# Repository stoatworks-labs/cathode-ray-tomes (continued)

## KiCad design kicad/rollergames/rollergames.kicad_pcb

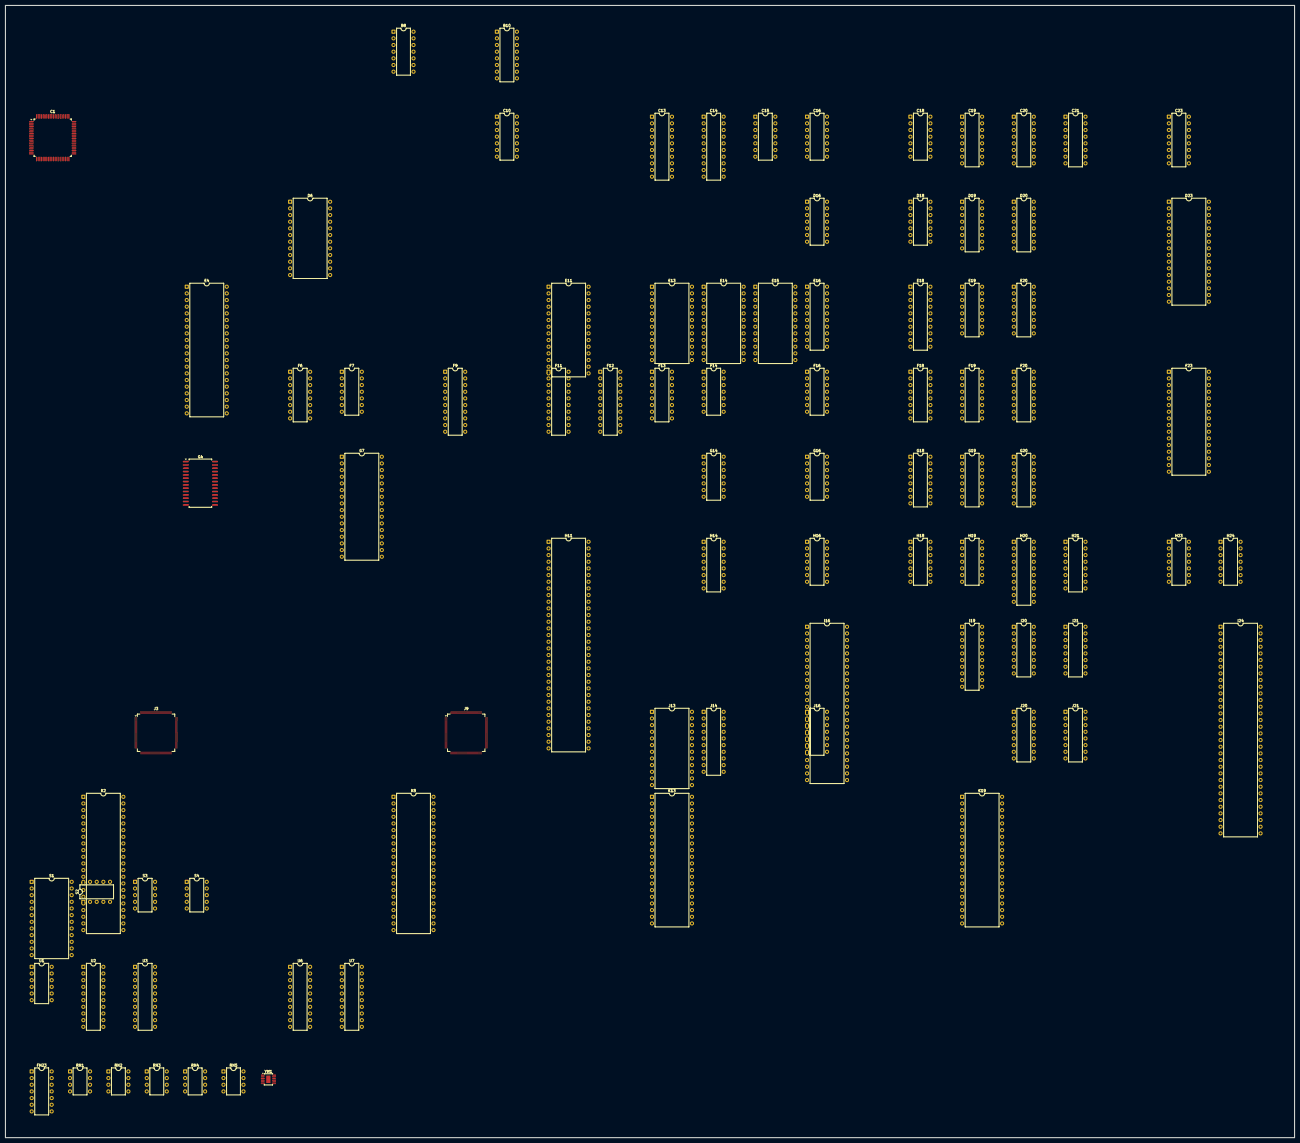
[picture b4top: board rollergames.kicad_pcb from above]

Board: 2 copper layers, 491.3 x 431.5 mm, 88 parts (0 on the bottom side), 516 nets, no tracks yet.

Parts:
B8: LM324; DIP-14_W7.62mm
B10: YM3012; DIP-16_W7.62mm
C1: 053260; PQFP-80_14x14mm_P0.65mm
C10: LM324; DIP-14_W7.62mm
C13, C14: 74LS273; DIP-20_W7.62mm
C15, C16, C18: 74LS07; DIP-14_W7.62mm
C19, C20, C21, C23: 74LS253; DIP-16_W7.62mm
D6: YM3812-3526; DIP-24_W15.24mm
D16: 74LS07; DIP-14_W7.62mm
D18: 74LS32; DIP-14_W7.62mm
D19, D20: 74LS257; DIP-16_W7.62mm
D23: 23C4000; DIP-32_W15.24mm
E4: Z80CPU; DIP-40_W15.24mm
E11: 27256; DIP-28_W15.24mm
E13: MB9416; DIP-24_W15.24mm
E14, E15: SRAM2K8B; DIP-24_W15.24mm
E16, E18: 74LS245; DIP-20_W7.62mm
E19: 74LS157; DIP-16_W7.62mm
E20: 63S141; DIP-16_W7.62mm
F6, F13: 74LS138; DIP-16_W7.62mm
F7, F14: 74LS04; DIP-14_W7.62mm
F9: 74LS245; DIP-20_W7.62mm
F11, F12: PAL16L8; DIP-20_W7.62mm
F16: 74LS08; DIP-14_W7.62mm
F18, F19: 74LS157; DIP-16_W7.62mm
F20: 74LS399; DIP-16_W7.62mm
F23: 23C4000; DIP-32_W15.24mm
FH23: 74LS08; DIP-14_W7.62mm
G4: MB8464A; SOP-28_8.4x18.16mm_P1.27mm
G7: 27C1000; DIP-32_W15.24mm
G14: 74LS74; DIP-14_W7.62mm
G16: 74LS32; DIP-14_W7.62mm
G18: 74LS174; DIP-16_W7.62mm
G19: 74LS367; DIP-16_W7.62mm
G20: 74LS399; DIP-16_W7.62mm
H11: 053248; DIP-64_W15.24mm
H14: 74LS367; DIP-16_W7.62mm
H16: 74LS04; DIP-14_W7.62mm
H18, H19: 74LS74; DIP-14_W7.62mm
H20: 74LS273; DIP-20_W7.62mm
H21: 74LS399; DIP-16_W7.62mm
H23: 74LS08; DIP-14_W7.62mm
H24: 74LS164; DIP-14_W7.62mm
I16: DIP-48_W15.24mm
I19: 74LS244; DIP-20_W7.62mm
I20: 74LS175; DIP-16_W7.62mm
I21: 74LS174; DIP-16_W7.62mm
I24: DIP-64_W15.24mm
J3: 053244; TQFP-120_14x14mm_P0.4mm
J9: 053245; TQFP-120_14x14mm_P0.4mm
J13: SRAM2K8B; DIP-24_W15.24mm
J14: 74LS245; DIP-20_W7.62mm
J16: 74LS04; DIP-14_W7.62mm
J20: 74LS175; DIP-16_W7.62mm
J21: 74LS174; DIP-16_W7.62mm
K2, K8: HN624116P; DIP-42_W15.24mm
K13, K19: 23C4100; DIP-40_W15.24mm
RN1, RN2, RN3, RN4, RN5: KONAMI_005273; DIP-8_W7.62mm
S1: 051550; DIP-24_W15.24mm
S2, S3, S4: 052535; DIP-10_W7.62mm
U1: MB3733-31; DIP-12_W7.62mm
U2, U3, U6, U7: 74LS244; DIP-20_W7.62mm
YM1: YM3014; MSOP-12-1EP_3x4.039mm_P0.65mm_EP1.651x2.845mm

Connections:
/+12V: S1.19, U1.11
/CLK1: I16.8, I24.2
/CLK2: C13.11, C14.11, F20.9, G20.9, H16.1, H19.3, H20.11, I16.9, J3.10, J9.10
/CLK4: I16.11, I24.63, J16.1
/COIN_CNT_1: S1.22, S1.23
/COIN_CNT_2: S1.20, S1.21
/CPU~EN: D19.2, G16.2, J9.26
/DB0: C1.8, C21.9, D19.9, J3.29, J14.2
/DB1: C1.9, C21.7, D19.12, J3.28, J14.3
/DB2: C1.10, C23.9, D19.7, J3.27, J14.4
/DB3: C1.11, C23.7, D19.4, J3.26, J14.5
/DB4: C1.13, C20.9, D20.9, J3.25, J14.6
/DB5: C1.14, C20.7, D20.12, J3.24, J14.7
/DB6: C1.15, C19.9, D20.7, J3.23, J14.8
/DB7: C1.16, C19.7, D20.4, J3.22, J14.9
/DTAC: F16.3, H11.49
/G18P7: E20.15, F12.2, G18.7
/G18P15: G16.4, G18.15
/IO_Cabinet/DW1_4: C23.6, C23.10
/IO_Cabinet/SMU: C19.14, C20.14, C21.14, C23.14, D19.1, D20.1, F14.4
/IO_Cabinet/SMUB: C19.2, C20.2, C21.2, C23.2, F14.2
/IO_Cabinet/VCC: C19.16, C20.16, C21.16, C23.16, D19.5, D19.11, D19.14, D19.16, D20.2, D20.5, D20.11, D20.14, D20.16
/M12B: H16.3, H16.12, H19.11, I21.9, J3.12, J9.12, J21.9
/MAIN_A0: D18.5, F7.13, F14.3, G4.2, G4.10, G4.23, G7.4, G7.12, G7.25, H11.14, I16.42, J3.19, J9.9, J21.3
/MAIN_A1: C1.18, F14.1, F18.2, G4.9, G7.11, H11.13, I16.41, J3.18, J9.25, J21.4
/MAIN_A2: F18.5, G4.8, G7.10, H11.12, I16.40, J3.17, J9.24, J21.6
/MAIN_A3: F18.11, G4.7, G7.9, H11.11, I16.38, J3.15, J9.23, J21.11
/MAIN_A4: F13.1, F18.14, G4.6, G7.8, H11.9, J9.22, J21.13
/MAIN_A5: F12.11, F13.2, F19.2, G4.5, G7.7, H11.8, J9.20, J21.14
/MAIN_A6: F12.9, F13.3, F19.5, G4.4, G7.6, H11.7, I21.3, J9.19
/MAIN_A7: F12.8, F19.11, G4.3, G7.5, H11.6, I21.4, J9.18
/MAIN_A8: F12.7, F19.14, G4.25, G7.27, H11.62, I21.6, J9.17
/MAIN_A9: E19.2, F12.6, G4.24, G7.26, H11.61, I21.11, J9.15
/MAIN_A10: E19.5, F12.5, G4.21, G7.23, H11.60, I21.13, J9.14
/MAIN_A11: F12.4, H11.59
/MAIN_A12: F11.5, F12.3, H11.56
/MAIN_A13: F11.4, H11.55
/MAIN_A14: F11.3, H11.54
/MAIN_A15: F11.2, H11.53
/MAIN_A16: F11.9, H11.38
/MAIN_A17: F11.8, H11.39
/MAIN_A18: F11.7, H11.40
/MAIN_A19: F11.6, H11.41
/MAIN_AB0: F11.14, G7.28
/MAIN_AB1: F11.15, G7.29
/MAIN_AB2: F11.16, G7.3
/MAIN_AB3: F11.17, G7.2
/MAIN_D0: F9.18, G4.11, G7.13, H11.21
/MAIN_D1: F9.17, G4.12, G7.14, H11.22
/MAIN_D2: F9.16, G4.13, G7.15, H11.23
/MAIN_D3: F9.15, G4.15, G7.17, H11.24
/MAIN_D4: F9.14, G4.16, G7.18, H11.27
/MAIN_D5: F9.13, G4.17, G7.19, H11.28
/MAIN_D6: F9.12, G4.18, G7.20, H11.29
/MAIN_D7: F9.11, G4.19, G7.21, H11.30
/MOE: C19.1, C19.15, C20.1, C20.15, C21.1, C21.15, C23.1, C23.15, F13.10
/Main/CRES: G18.1, H14.4, I16.12
/Main/DB0: F9.2, G18.3, I16.13
/Main/DB1: F9.3, G18.4, I16.14
/Main/DB2: F9.4, G18.6, I16.15
/Main/DB3: F9.5, G18.11, I16.16
/Main/DB4: F9.6, G18.13, I16.18
/Main/DB5: F9.7, G18.14, I16.19
/Main/DB6: F9.8, I16.20
/Main/DB7: F9.9, I16.21
/Main/MPE: H11.51, H14.7
/Main/MPQ: H11.17, H14.3
/Main/PAL12: F12.12, F13.4
/Main/PE: H14.2, I16.1
/Main/PQ: H16.5, I16.2
/Main/RCLK: F13.13, S1.1
/Main/RESET: H11.2, H14.5
/Main/VCC: F11.20, F12.20, F13.6, F13.16, G18.16, H11.26, H11.50, H11.58, H14.16, I16.3, I16.4, I16.17, I16.39
/Main/~CCO: F12.13, I16.36
/Main/~IRQ: H11.4, I16.34
/Not_Populated/OBJROMA0: K13.9, K19.9
/Not_Populated/OBJROMA1: K13.8, K19.8
/Not_Populated/OBJROMA2: K13.7, K19.7
/Not_Populated/OBJROMA3: K13.6, K19.6
/Not_Populated/OBJROMA4: K13.5, K19.5
/Not_Populated/OBJROMA5: K13.4, K19.4
/Not_Populated/OBJROMA6: K13.3, K19.3
/Not_Populated/OBJROMA7: K13.2, K19.2
/Not_Populated/OBJROMA8: K13.40, K19.40
/Not_Populated/OBJROMA9: K13.39, K19.39
/Not_Populated/OBJROMA10: K13.38, K19.38
/Not_Populated/OBJROMA11: K13.37, K19.37
/Not_Populated/OBJROMA12: K13.36, K19.36
/Not_Populated/OBJROMA13: K13.35, K19.35
/Not_Populated/OBJROMA14: K13.34, K19.34
/Not_Populated/OBJROMA15: K13.33, K19.33
/Not_Populated/OBJROMA16: K13.32, K19.32
/Not_Populated/OBJROMA17: K13.1, K19.1
/Not_Populated/OBJROMD0: K13.13, U6.18
/Not_Populated/OBJROMD1: K13.15, U6.16
/Not_Populated/OBJROMD2: K13.17, U6.14
/Not_Populated/OBJROMD3: K13.19, U6.12
/Not_Populated/OBJROMD4: K13.22, U6.3
/Not_Populated/OBJROMD5: K13.24, U6.5
/Not_Populated/OBJROMD6: K13.26, U6.7
/Not_Populated/OBJROMD7: K13.28, U6.9
/Not_Populated/OBJROMD8: K19.13, U2.18
/Not_Populated/OBJROMD9: K19.15, U2.16
/Not_Populated/OBJROMD10: K19.17, U2.14
/Not_Populated/OBJROMD11: K19.19, U2.12
/Not_Populated/OBJROMD12: K19.22, U2.3
/Not_Populated/OBJROMD13: K19.24, U2.5
/Not_Populated/OBJROMD14: K19.26, U2.7
/Not_Populated/OBJROMD15: K19.28, U2.9
/Not_Populated/OBJROMD16: K13.14, U7.18
/Not_Populated/OBJROMD17: K13.16, U7.16
/Not_Populated/OBJROMD18: K13.18, U7.14
/Not_Populated/OBJROMD19: K13.20, U7.12
/Not_Populated/OBJROMD20: K13.23, U3.3, U7.3
/Not_Populated/OBJROMD21: K13.25, U3.5, U7.5
/Not_Populated/OBJROMD22: K13.27, U3.7, U7.7
/Not_Populated/OBJROMD23: K13.29, U3.9, U7.9
/Not_Populated/OBJROMD24: K19.14, U3.18
/Not_Populated/OBJROMD25: K19.16, U3.16
/Not_Populated/OBJROMD26: K19.18, U3.14
/Not_Populated/OBJROMD27: K19.20, U3.12
/Not_Populated/VCC: K13.21, K13.31, K19.21, K19.31
/Not_Populated/VSS: K13.10, K13.11, K13.30, K19.10, K19.11, K19.30
/OBCE: D18.6, D18.9, E18.19
/OBJOE: F12.16, I19.1, I19.19
/OBJPXL0: F20.4, J3.120
/OBJPXL1: F20.5, J3.119
/OBJPXL2: F20.12, J3.118
/OBJPXL3: F20.13, J3.117
/OBJPXL4: G20.4, J3.116
/OBJPXL5: G20.5, J3.115
/OBJPXL6: G20.12, J3.114
/OBJPXL7: G20.13, J3.113
/OBJSE: D18.1, D18.4, E19.1, F12.19, F16.1, F18.1, F19.1
/OBOB: E20.2, J3.112
/OBOK: E20.3, J3.107
/OOE: F11.19, G7.24
/Objects/AR0: J3.30, J9.119
/Objects/AR1: J3.32, J9.118
/Objects/AR2: J3.33, J9.117
/Objects/AROK: J3.34, J9.116
/Objects/BR0: J3.35, J9.115
/Objects/BR1: J3.36, J9.114
/Objects/BR2: J3.37, J9.113
/Objects/BROK: J3.38, J9.112
/Objects/CLAT: J3.64, J9.86
/Objects/HP0: J3.54, J9.96
/Objects/HP1: J3.53, J9.97
/Objects/HP2: J3.52, J9.98
/Objects/HP3: J3.50, J9.99
/Objects/HP4: J3.49, J9.100
/Objects/HP5: J3.48, J9.102
/Objects/HP6: J3.47, J9.103
/Objects/HP7: J3.45, J9.104
/Objects/HP8: J3.44, J9.105
/Objects/HP9: J3.43, J9.107
/Objects/HRFP: J3.39, J9.110
/Objects/OBJRAMD0: J9.45, J13.9, J14.18
/Objects/OBJRAMD1: J9.44, J13.10, J14.17
/Objects/OBJRAMD2: J9.43, J13.11, J14.16
/Objects/OBJRAMD3: J9.42, J13.13, J14.15
/Objects/OBJRAMD4: J9.40, J13.14, J14.14
/Objects/OBJRAMD5: J9.39, J13.15, J14.13
/Objects/OBJRAMD6: J9.38, J13.16, J14.12
/Objects/OBJRAMD7: J9.37, J13.17, J14.11
/Objects/OBJROMA0: J9.85, K2.10, K8.10
/Objects/OBJROMA1: J9.84, K2.9, K8.9
/Objects/OBJROMA2: J9.83, K2.8, K8.8
/Objects/OBJROMA3: J9.82, K2.7, K8.7
/Objects/OBJROMA4: J9.80, K2.6, K8.6
/Objects/OBJROMA5: J9.79, K2.5, K8.5
/Objects/OBJROMA6: J9.78, K2.4, K8.4
/Objects/OBJROMA7: J9.77, K2.3, K8.3
/Objects/OBJROMA8: J9.75, K2.41, K8.41
/Objects/OBJROMA9: J9.74, K2.40, K8.40
/Objects/OBJROMA10: J9.73, K2.39, K8.39
/Objects/OBJROMA11: J9.72, K2.38, K8.38
/Objects/OBJROMA12: J9.70, K2.37, K8.37
/Objects/OBJROMA13: J9.69, K2.36, K8.36
/Objects/OBJROMA14: J9.68, K2.35, K8.35
/Objects/OBJROMA15: J9.67, K2.34, K8.34
/Objects/OBJROMA16: J9.66, K2.33, K8.33
/Objects/OBJROMA17: J9.65, K2.2, K8.2
/Objects/OBJROMA18: J9.64, K2.1, K8.1
/Objects/OBJROMD0: J3.100, K2.14
/Objects/OBJROMD1: J3.99, K2.16
/Objects/OBJROMD2: J3.98, K2.18
/Objects/OBJROMD3: J3.97, K2.20
/Objects/OBJROMD4: J3.96, K2.23
/Objects/OBJROMD5: J3.95, K2.25
/Objects/OBJROMD6: J3.94, K2.27
/Objects/OBJROMD7: J3.93, K2.29
/Objects/OBJROMD8: J3.92, K8.14
/Objects/OBJROMD9: J3.90, K8.16
/Objects/OBJROMD10: J3.89, K8.18
/Objects/OBJROMD11: J3.88, K8.20
/Objects/OBJROMD12: J3.87, K8.23
/Objects/OBJROMD13: J3.86, K8.25
/Objects/OBJROMD14: J3.85, K8.27
/Objects/OBJROMD15: J3.84, K8.29
/Objects/OBJROMD16: J3.83, K2.15
/Objects/OBJROMD17: J3.82, K2.17
/Objects/OBJROMD18: J3.80, K2.19
/Objects/OBJROMD19: J3.79, K2.21
/Objects/OBJROMD20: J3.78, K2.24
/Objects/OBJROMD21: J3.77, K2.26
/Objects/OBJROMD22: J3.75, K2.28
/Objects/OBJROMD23: J3.74, K2.30
/Objects/OBJROMD24: J3.73, K8.15
/Objects/OBJROMD25: J3.72, K8.17
/Objects/OBJROMD26: J3.70, K8.19
/Objects/OBJROMD27: J3.69, K8.21
/Objects/OBJROMD28: J3.68, K8.24
/Objects/OBJROMD29: J3.67, K8.26
/Objects/OBJROMD30: J3.66, K8.28
/Objects/OBJROMD31: J3.65, K8.30
/Objects/ORAMA0: J9.50, J13.1
/Objects/ORAMA1: J9.52, J13.4
/Objects/ORAMA2: J9.53, J13.5
/Objects/ORAMA3: J9.54, J13.23
/Objects/ORAMA4: J9.55, J13.6
/Objects/ORAMA5: J9.56, J13.22
/Objects/ORAMA6: J9.57, J13.7
/Objects/ORAMA7: J9.58, J13.8
/Objects/ORAMA8: J9.59, J13.19
/Objects/ORAMA9: J9.62, J13.3
/Objects/ORAMA10: J9.63, J13.2
/Objects/PL0: J3.63, J9.87
/Objects/PL1: J3.62, J9.88
/Objects/PL2: J3.60, J9.89
/Objects/PL3: J3.59, J9.90
/Objects/PL4: J3.58, J9.92
/Objects/PL5: J3.57, J9.93
/Objects/PL6: J3.56, J9.94
/Objects/R~OE: J9.49, J13.20
/Objects/SHADOW: J3.55, J9.95
/Objects/~HIT: J3.42, J9.108
/Objects/~WE1: J9.48, J13.21
/Objects/~ZLD: J3.40, J9.109
/PAL14: F12.14, H23.2
/PAL17: F12.17, H23.1
/PSAC/63S1: E20.12, F20.1, G20.1, H20.18
/PSAC/63S2: E20.11, H20.17
/PSAC/+5V: I24.32, I24.64
/PSAC/CA0: I24.31, J16.5
/PSAC/CA1: D23.12, F23.12, I24.30
/PSAC/CA2: D23.11, F23.11, I24.29
/PSAC/CA3: D23.10, F23.10, I24.28
/PSAC/CA4: D23.9, F23.9, I24.27
/PSAC/CA5: D23.8, F23.8, I24.26
/PSAC/CA6: D23.7, F23.7, I24.25
/PSAC/CA7: D23.6, F23.6, I24.24
/PSAC/CA8: D23.5, F23.5, I24.23
/PSAC/CA9: D23.27, F23.27, I24.22
/PSAC/CA10: D23.26, F23.26, I24.21
/PSAC/CA11: D23.23, F23.23, I24.20
/PSAC/CA12: D23.25, F23.25, I24.19
/PSAC/CA13: D23.4, F23.4, I24.18
/PSAC/CA14: D23.28, F23.28, I24.17
/PSAC/CA15: D23.29, F23.29, I24.15
/PSAC/CA16: D23.3, F23.3, I24.14
/PSAC/CA17: D23.2, F23.2, I24.13
/PSAC/CA18: D23.30, F23.30, I24.12
/PSAC/CA19: D23.24, I24.11
/PSAC/CA20: I24.10, J20.4
/PSAC/CA21: I24.9, J20.5
/PSAC/DB0: I19.18, I24.50
/PSAC/DB1: I19.16, I24.51
/PSAC/DB2: I19.14, I24.52
/PSAC/DB3: I19.12, I24.53
/PSAC/DB4: I19.9, I24.54
/PSAC/DB5: I19.7, I24.55
/PSAC/DB6: I19.5, I24.56
/PSAC/DB7: I19.3, I24.57
/PSAC/HRC: I20.6, I24.62
/PSAC/HSCM: I20.15, I24.60
/PSAC/OBLK: G16.5, I24.4
/PSAC/PA0: I24.36, J21.2
/PSAC/PA1: I24.37, J21.5
/PSAC/PA2: I24.38, J21.7
/PSAC/PA3: I24.39, J21.10
/PSAC/PA4: I24.40, J21.12
/PSAC/PA5: I24.41, J21.15
/PSAC/PA6: I21.2, I24.42
/PSAC/PA7: I21.5, I24.43
/PSAC/PA8: I21.7, I24.44
/PSAC/PA9: I21.10, I24.45
/PSAC/PA10: I21.12, I24.46
/PSAC/POBJ0: F18.3, F20.2
/PSAC/POBJ1: F18.6, F20.7
/PSAC/POBJ2: F18.10, F20.10
/PSAC/POBJ3: F18.13, F20.15
/PSAC/POBJ4: F19.3, G20.2
/PSAC/POBJ5: F19.6, G20.7
/PSAC/POBJ6: F19.10, G20.10
/PSAC/POBJ7: F19.13, G20.15
/PSAC/PRAM0: D23.13, F23.13, H21.3, I19.2
/PSAC/PRAM1: D23.14, F23.14, H21.6, I19.4
/PSAC/PRAM2: D23.15, F23.15, H21.11, I19.6
/PSAC/PRAM3: D23.17, F23.17, H21.14, I19.8
/PSAC/PRAM4: D23.18, F23.18, H21.4, I19.11
/PSAC/PRAM5: D23.19, F23.19, H21.5, I19.13
/PSAC/PRAM6: D23.20, F23.20, H21.12, I19.15
/PSAC/PRAM7: D23.21, F23.21, H21.13, I19.17
/PSAC/RGB/COLA0: E14.8, E15.6, F19.12
/PSAC/RGB/COLA1: E14.7, E15.5, F19.7
/PSAC/RGB/COLA2: E14.6, E15.4, F18.12
/PSAC/RGB/COLA3: E14.5, E15.3, E19.7
/PSAC/RGB/COLA4: E14.4, E15.2, F18.4
/PSAC/RGB/COLA5: E14.3, E15.22, E19.4
/PSAC/RGB/COLA6: E14.2, E15.23, F18.7
/PSAC/RGB/COLA7: E14.1, E15.1, F18.9
/PSAC/RGB/COLA8: E14.23, E15.8, F19.4
/PSAC/RGB/COLA9: E14.22, E15.7, F19.9
/PSAC/RGB/COLABR0: C14.3, E15.9, E16.18
/PSAC/RGB/COLABR1: C14.4, E15.10, E16.17
/PSAC/RGB/COLABR2: C14.7, E15.11, E16.16
/PSAC/RGB/COLABR3: C14.8, E15.13, E16.15
/PSAC/RGB/COLABR4: C14.13, E15.14, E16.14
/PSAC/RGB/COLABR5: C14.14, E15.15, E16.13
/PSAC/RGB/COLABR6: C14.17, E15.16, E16.12
/PSAC/RGB/COLABR7: C14.18, E15.17, E16.11
/PSAC/RGB/COLAR0: C13.3, E14.9, E18.18
/PSAC/RGB/COLAR1: C13.4, E14.10, E18.17
/PSAC/RGB/COLAR2: C13.7, E14.11, E18.16
/PSAC/RGB/COLAR3: C13.8, E14.13, E18.15
/PSAC/RGB/COLAR4: C13.13, E14.14, E18.14
/PSAC/RGB/COLAR5: C13.14, E14.15, E18.13
/PSAC/RGB/COLAR6: C13.17, E14.16, E18.12
/PSAC/RGB/COLAR7: C13.18, E14.17, E18.11
/PSAC/RGB/DB0: E16.2, E18.2
/PSAC/RGB/DB1: E16.3, E18.3
/PSAC/RGB/DB2: E16.4, E18.4
/PSAC/RGB/DB3: E16.5, E18.5
/PSAC/RGB/DB4: E16.6, E18.6
/PSAC/RGB/DB5: E16.7, E18.7
/PSAC/RGB/DB6: E16.8, E18.8
/PSAC/RGB/DB7: E16.9, E18.9
/PSAC/RGB/POE: E14.20, E15.20, E19.9
/PSAC/VD0: G19.2, H20.2
/PSAC/VD1: G19.4, H20.5
/PSAC/VD2: G19.6, H20.6
/PSAC/VD3: G19.10, H20.9
/PSAC/VD4: G19.12, H20.12
/PSAC/VD5: G19.14, H20.15
/PSAC/VD7: E19.3, H20.19
/PSAC/VDR1: E20.5, F20.3, G19.3
/PSAC/VDR2: E20.6, F20.6, G19.5
/PSAC/VDR3: E20.7, F20.11, G19.7
/PSAC/VDR4: E20.4, F20.14, G19.9
/PSAC/VDR5: G19.11, G20.3
/PSAC/VDR6: G19.13, G20.6
/PSAC/VRC: I20.3, I24.61
/PSAC/VSCM: I20.10, I24.59
/PSAC/~CA19: D18.2, F7.12, F23.24
/RES: B10.7, C1.75, D6.3, E4.26, F16.12, G14.1, I16.7, J3.3, J9.3, J20.1, S1.10
/R/~W: C1.19, F9.1, F11.11, G4.27, G16.9, H11.15, I16.37, I24.58
/SDI0: E20.1, J3.108
/SND_INT: F13.11, G14.11
/Sound/PCMCLK: C1.21, D6.24, F7.8
/Sound/PCM~CS: C1.72, F6.10
/Sound/SH1: B10.6, C1.26, G14.3
/Sound/SH2: B10.5, C1.27
/Sound/SND_A0: C1.70, D6.4, E4.30, E11.10, E13.19
/Sound/SND_A1: C1.69, E4.31, E11.9, E13.8
/Sound/SND_A2: C1.68, E4.32, E11.8, E13.4
/Sound/SND_A3: C1.67, E4.33, E11.7, E13.7
/Sound/SND_A4: C1.66, E4.34, E11.6, E13.6
/Sound/SND_A5: C1.65, E4.35, E11.5, E13.5
/Sound/SND_A6: E4.36, E11.4, E13.23
/Sound/SND_A7: E4.37, E11.3, E13.22
/Sound/SND_A8: E4.38, E11.25, E13.3
/Sound/SND_A9: E4.39, E11.24, E13.2
/Sound/SND_A10: E4.40, E11.21, E13.1
/Sound/SND_A11: E4.1, E11.23
/Sound/SND_A12: E4.2, E11.2
/Sound/SND_A13: E4.3, E11.26, F6.1
/Sound/SND_A14: E4.4, E11.27, F6.2
/Sound/SND_A15: E4.5, E11.20, F6.3
/Sound/SNS_D0: C1.5, D6.10, E4.14, E11.11, E13.9
/Sound/SNS_D1: C1.4, D6.11, E4.15, E11.12, E13.10
/Sound/SNS_D2: C1.3, D6.13, E4.12, E11.13, E13.11
/Sound/SNS_D3: C1.2, D6.14, E4.8, E11.15, E13.13
/Sound/SNS_D4: C1.1, D6.15, E4.7, E11.16, E13.14
/Sound/SNS_D5: C1.80, D6.16, E4.9, E11.17, E13.15
/Sound/SNS_D6: C1.79, D6.17, E4.10, E11.18, E13.16
/Sound/SNS_D7: C1.78, D6.18, E4.13, E11.19, E13.17
/Sound/SY: B10.2, C1.25
/Sound/~INT: E4.16, G14.8
/Sound/~IORQ: E4.20, F16.13
/Sound/~MREQ: E4.19, F6.4
/Sound/~NMI: E4.17, G14.5
/Sound/~RFSH: E4.28, F6.6
/VD6: F14.11, H20.16
/WR: D18.8, E14.21
/ZOE: D19.15, D20.15, F13.9
/~AS: F11.1, H11.16, H18.12, J16.11
/~CLK2: H11.18, H16.2, H16.13
/~CS1: F11.13, G4.20
/~DS: D18.10, D18.13, H11.20, J3.14
/~HBK: H24.1, I16.33, I20.13
/~HSYNC: I16.29, I20.5, J3.8, J9.4
/~MCS: C1.17, F13.12
/~OBJSET: F12.15, F14.5, F16.9, J3.13, J9.6
/~OBJ_CS: F12.18, F14.10, F16.10, G16.10
/~RD: D6.6, E4.21, E11.22, E13.20, E16.1, E18.1, E19.11, F7.3, G4.22, G16.13, J3.20, J9.13
/~VBK: H24.2, I16.27, I20.12
/~VSYNC: C18.5, I16.26, I20.4, J3.9, J9.5
GNDPWR: B8.11, B10.3, B10.8, B10.16, C1.12, C1.34, C1.43, C1.52, C1.61, C1.74, C10.11, C13.10, C14.10, C15.7, C16.7, C18.7, C19.8, C20.8, C21.8, C23.8, D6.12, D16.7, D18.7, D19.8, D20.8, D23.16, D23.22, E4.29, E11.14, E13.12, E14.12, E14.18, E14.19, E15.12, E15.18, E15.19, E19.6, E19.10, E19.15, E20.8, E20.13, E20.14, F6.5, F6.8, F7.7, F11.10, F12.10, F13.5, F13.8, F14.7, F16.7, F18.15, F19.15, F20.8, F23.16, F23.22, FH23.7, G4.14, G7.16, G7.22, G14.2, G14.7, G16.7, G18.8, G19.8, G20.8, G20.11, G20.14, H11.1, H11.5, H11.10, H11.19, H11.25, H11.31, H11.32, H11.33, H11.34, H11.35, H11.36, H11.37, H11.42, H11.47, H11.48, H11.52, H11.57, H14.1, H14.8, H16.7, H18.7, H19.7, H20.10, H21.8, H23.7, I16.6, I16.22, I16.23, I16.28, I16.43, I19.10, I20.8, I21.8, I24.3, I24.16, I24.35, I24.48, J3.1, J3.2, J3.11, J3.21, J3.31, J3.41, J3.51, J3.61, J3.71, J3.81, J3.91, J3.101, J3.111, J9.1, J9.2, J9.8, J9.11, J9.21, J9.31, J9.41, J9.51, J9.61, J9.71, J9.81, J9.91, J9.101, J9.111, J13.12, J13.18, J16.7, J20.8, J21.8, K2.11, K2.12, K2.13, K2.31, K8.11, K8.12, K8.13, K8.31, S1.13, S1.14, S2.9, S3.9, S4.9, U1.3, U1.7, YM1.6
unnamed: B8.6, B8.7
unnamed: B8.2, B10.14
unnamed: B8.5, B10.12
unnamed: B8.1, B10.13
unnamed: B8.3, B10.15
unnamed: C1.71, F7.4
unnamed: C10.10, YM1.2
unnamed: C10.8, C10.9
unnamed: C10.12, YM1.7
unnamed: C10.13, C10.14
unnamed: C13.2, C16.3
unnamed: C13.5, C15.1
unnamed: C13.6, C15.9
unnamed: C13.9, D16.11
unnamed: C13.12, D16.13
unnamed: C13.15, C15.11
unnamed: C13.16, C15.5
unnamed: C13.19, C16.1
unnamed: C14.2, C15.13
unnamed: C14.5, C16.9
unnamed: C14.6, C15.3
unnamed: C14.9, D16.9
unnamed: C14.12, D16.3
unnamed: C14.15, C16.13
unnamed: C14.16, C16.11
unnamed: C14.19, C16.5
unnamed: C19.5, RN2.1
unnamed: C19.11, RN2.3
unnamed: C19.4, RN1.3
unnamed: C19.12, RN1.7
unnamed: C19.3, RN1.1
unnamed: C19.13, RN1.5
unnamed: C20.5, RN2.5
unnamed: C20.11, RN2.7
unnamed: C20.4, RN3.3
unnamed: C20.12, RN3.7
unnamed: C20.3, RN3.1
unnamed: C20.13, RN3.5
unnamed: C21.4, RN4.3
unnamed: C21.12, RN4.7
unnamed: C21.3, RN4.1
unnamed: C21.13, RN4.5
unnamed: C23.4, RN5.3
unnamed: C23.12, RN5.7
unnamed: C23.3, RN5.1
unnamed: C23.13, RN5.5
unnamed: D6.21, YM1.4
unnamed: D6.20, YM1.3
unnamed: D6.7, F6.9
unnamed: D6.5, E4.22, E13.21
unnamed: D6.23, YM1.5
unnamed: E13.18, F6.11
unnamed: D18.11, E15.21
unnamed: D18.3, D18.12, E16.19
unnamed: F6.7, G14.4
unnamed: F9.19, F11.18
unnamed: F11.12, F12.1
unnamed: F13.14, G18.9
unnamed: F14.6, G16.12
unnamed: F16.8, G16.1
unnamed: F16.11, G14.13
unnamed: G18.2, S1.15
unnamed: G18.5, S1.16
unnamed: G19.1, G19.15, H19.5
unnamed: H14.6, H16.6
unnamed: H16.4, H18.3
unnamed: H18.2, H23.3
unnamed: F16.4, H18.6
unnamed: H18.1, H18.10, H19.10, J16.10
unnamed: H18.11, H21.9, I20.9, J16.2, J20.9
unnamed: F16.5, H18.9
unnamed: H19.2, J20.14
unnamed: F16.6, H19.12
unnamed: F16.2, H19.9
unnamed: H20.3, H21.2
unnamed: H20.4, H21.7
unnamed: H20.7, H21.10
unnamed: H20.8, H21.15
unnamed: H20.13, J20.2
unnamed: H20.14, J20.7
unnamed: H21.1, J16.6
unnamed: C18.1, C18.3, C18.13, H24.5
unnamed: I16.5, J16.4
unnamed: D16.1, I16.25
unnamed: G16.8, J9.7
unnamed: G16.11, J14.1
unnamed: G16.3, J14.19
unnamed: G16.6, J20.13
unnamed: C15.12, S2.6
unnamed: C16.8, S2.5
unnamed: C15.4, S2.4
unnamed: D16.8, S2.3
unnamed: D16.4, S2.2
unnamed: C18.2, S2.7
unnamed: C16.12, S3.6
unnamed: C16.10, S3.5
unnamed: C16.6, S3.4
unnamed: C16.4, S3.3
unnamed: C15.2, S3.2
unnamed: C18.4, S3.7
unnamed: C15.8, S4.6
unnamed: D16.10, S4.5
unnamed: D16.12, S4.4
unnamed: C15.10, S4.3
unnamed: C15.6, S4.2
unnamed: C18.12, S4.7
VCC: B8.4, B10.1, C1.20, C1.33, C1.73, C10.4, C13.1, C13.20, C14.1, C14.20, C15.14, C16.14, C18.14, D6.1, D16.14, D18.14, D23.32, E4.11, E11.1, E11.28, E13.24, E14.24, E15.24, E20.16, F6.16, F7.14, F14.14, F16.14, F20.16, F23.32, FH23.14, G4.26, G4.28, G7.1, G7.31, G7.32, G14.10, G14.12, G14.14, G16.14, G19.16, G20.16, H16.14, H18.4, H18.13, H18.14, H19.1, H19.4, H19.13, H19.14, H20.1, H20.20, H21.16, H23.14, H24.9, H24.14, I19.20, I20.1, I20.16, I21.1, I21.16, J3.16, J3.46, J3.76, J3.106, J9.16, J9.46, J9.60, J9.76, J9.106, J9.120, J13.24, J16.14, J20.16, J21.1, J21.16, K2.22, K2.32, K2.42, K8.22, K8.32, K8.42, S1.9, S2.1, S3.1, S4.1, YM1.1

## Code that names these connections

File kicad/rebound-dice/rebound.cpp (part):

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		Signals
	**************************************************************************/	
    #define CLK "J4", 5
    #define CLK_n "J4", 6

	#define H1 "H5", 12
	#define H2 "H5", 9
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	#define H128 "F5", 11
	
	#define H256 "H4", 3
	#define H256_n "H4", 2
	
	#define HRESET "J4", 8
	#define HRESET_n "J4", 9
	
    #define HBLANK "K5", 5
	#define HBLANK_n "K5", 6
	
	#define HSYNC "K5", 9
	#define HSYNC_n "K5", 8

	#define V1 "J3", 12
	#define V2 "J3", 9
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	#define V128 "H3", 11

	#define V256 "H4", 5
	#define V256_n "H4", 6
	
	#define VRESET "J2", 8
	#define VRESET_n "J2", 9
	
	#define VSYNC_n "H1", 11
	
	#define NET_n "B8", 12
	#define PADDLE_12 "K6", 10
	#define NET_HEIGHT_n "B5", 10
	
	#define STOP1_n "F7", 8
	#define STOP2_n "F7", 6
	
	#define DISP_PAD1_n "B8", 6
	#define DISP_PAD2_n "B8", 8
	
	#define BACKWARDS_n "D6", 5
	#define DP "C6", 5
	#define CP_n "D6", 8
	#define BP_n "C6", 8
	
	#define V64_n "C8", 13
	
	#define HIT "E6", 10
	#define HIT_n "D5", 3
	
	#define SERVE "J1", 8
	#define SERVE_n "J1", 9
	#define SERVE_TIME "K1", 6
	#define SERVE_TIME_n "K1", 7
	
	#define RIGHT_SCORE "A1", 11
	#define LEFT_SCORE "A1", 3
	
	#define BALL_RETURN "J5", 3
	#define MISS_n "D2", 1
	
	#define BALL "E6", 4
	#define BALL_n "E6", 1
	
	#define LSB1 "K9", 12
	#define LSB2 "J9", 12
	#define STOP "J6", 8
	
	#define ATTRACT "E8", 5
	#define ATTRACT_n "E8", 6 
	
	#define START "E7", 9 
	#define START_n "E7", 8

	
	/**************************************************************************
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    CONNECTION("VIDEO", 2, "H8", 8)
    CONNECTION("VIDEO", 3, BALL)

    CONNECTION("VIDEO", Video::HBLANK_PIN, HBLANK)
    CONNECTION("VIDEO", Video::VBLANK_PIN, "H1", 3)

    // Audio Summing
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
